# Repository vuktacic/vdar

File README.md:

# vdar

vdar is a low-cost 3D lidar scanner using the TF-Luna. It can generate point clouds of it's environment, which can be visualized with [vvis](./vvis). vdar is completely open source, and was designed for Hack Club's [Stasis program](https://stasis.hackclub.com). vdar was also exhibited at [Open Sauce 2026](https://www.opensauce.com/)

I created vdar because of a general interest in LiDAR. I've been playing with point clouds for a few years, and wanted to create a device that could generate my own clouds. I also wanted to learn how to create a mechanically more complex design, combined with designing and manufacturing an actual PCB.

[vdar Youtube Video](https://www.youtube.com/shorts/brxcMjVyBjw)

## Repo Structure

- [`./hardware`](./hardware) - Design files for vdar
  - [`./hardware/cad`](./hardware/cad) - Fusion 360 & Step design files for vdar
  - [`./hardware/pcb`](./hardware/pcb) - KiCad design files for vdar
    - [`./hardware/pcb/production`](./hardware/pcb/production) - PCB Production files (gerbers.zip)
- [`./JOURNAL.md`](./JOURNAL.md) - Development Journal for vdar
- [`./project`](./project) - Project management files for vdar
    - [`./project/assets`](./project/assets) - Media for project files
    - [`./project/docs`](./project/docs) - Assembly instructions for vdar
    - [`./project/finances`](./project/finances) - BOM & POs for vdar
- [`./vcore`](./vcore) - ESP32 firmware for vdar
- [`./vvis`](./vvis) - NodeJS visualizer for vdar

## Quick Start
Requirements:
 - PlatformIO Core
 - NodeJS
 - Python3

```bash
git clone https://github.com/vuktacic/vdar.git
cd vdar
just setup
mv ./vcore/include/secrets.h.example ./vcore/include/secrets.h
```
```bash
just build
just flash
just run
```

## Pictures
### Real life

### Scans

### 3D CAD

### PCB

### Offboard Wiring

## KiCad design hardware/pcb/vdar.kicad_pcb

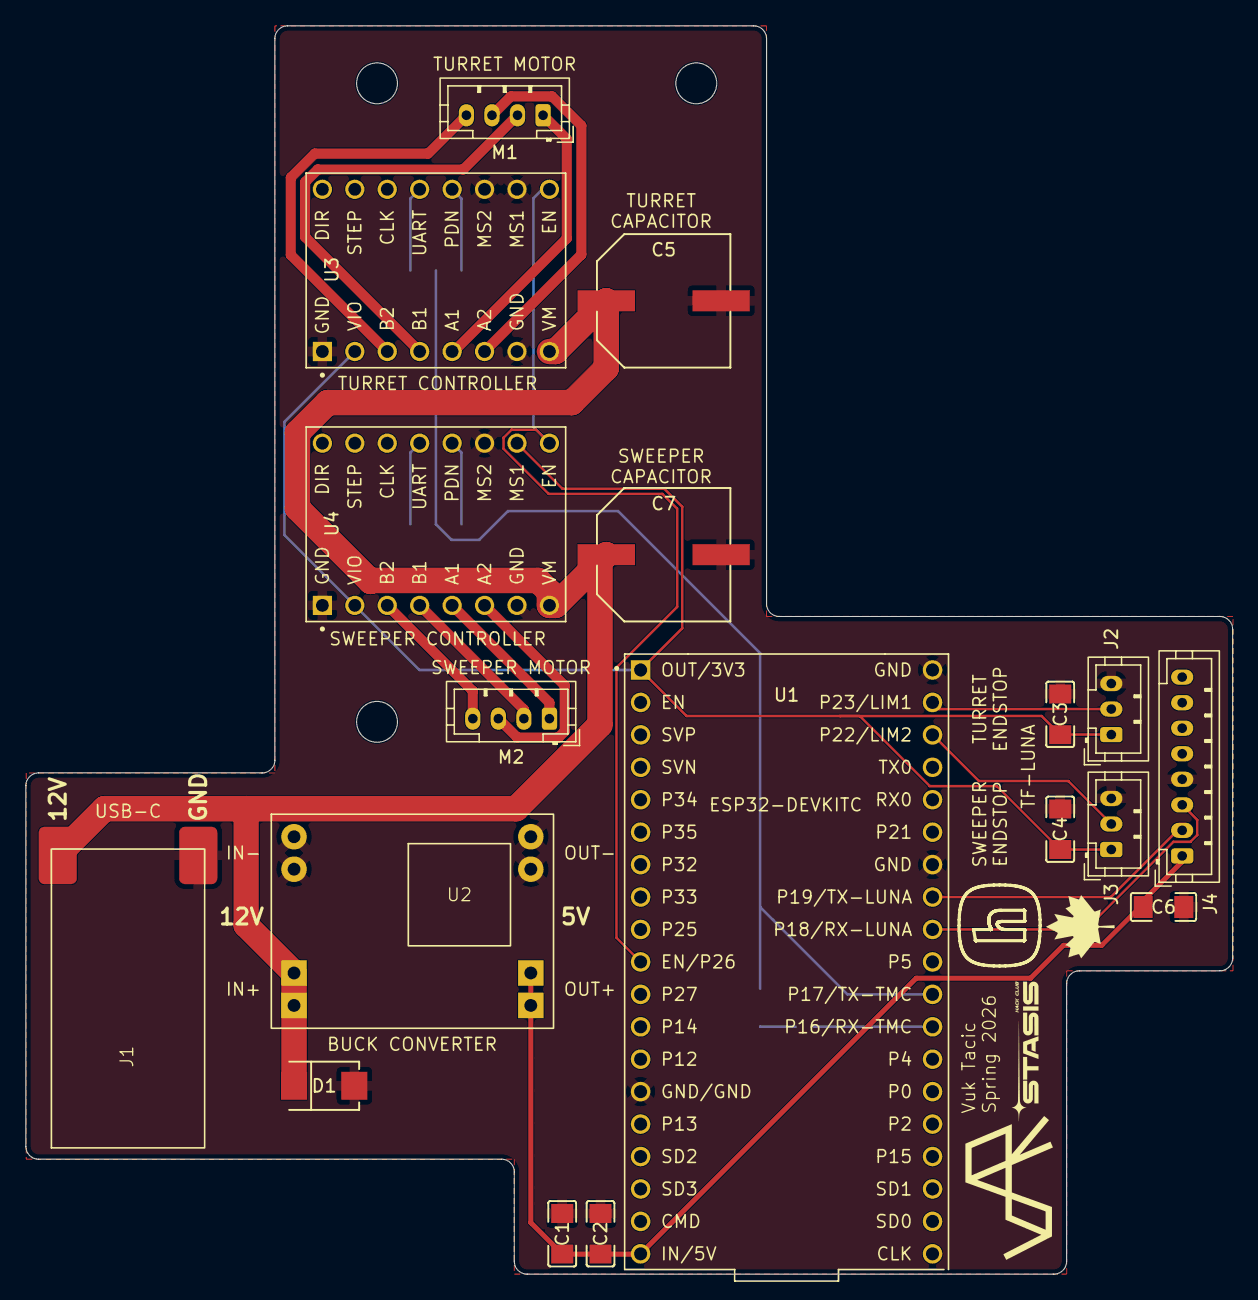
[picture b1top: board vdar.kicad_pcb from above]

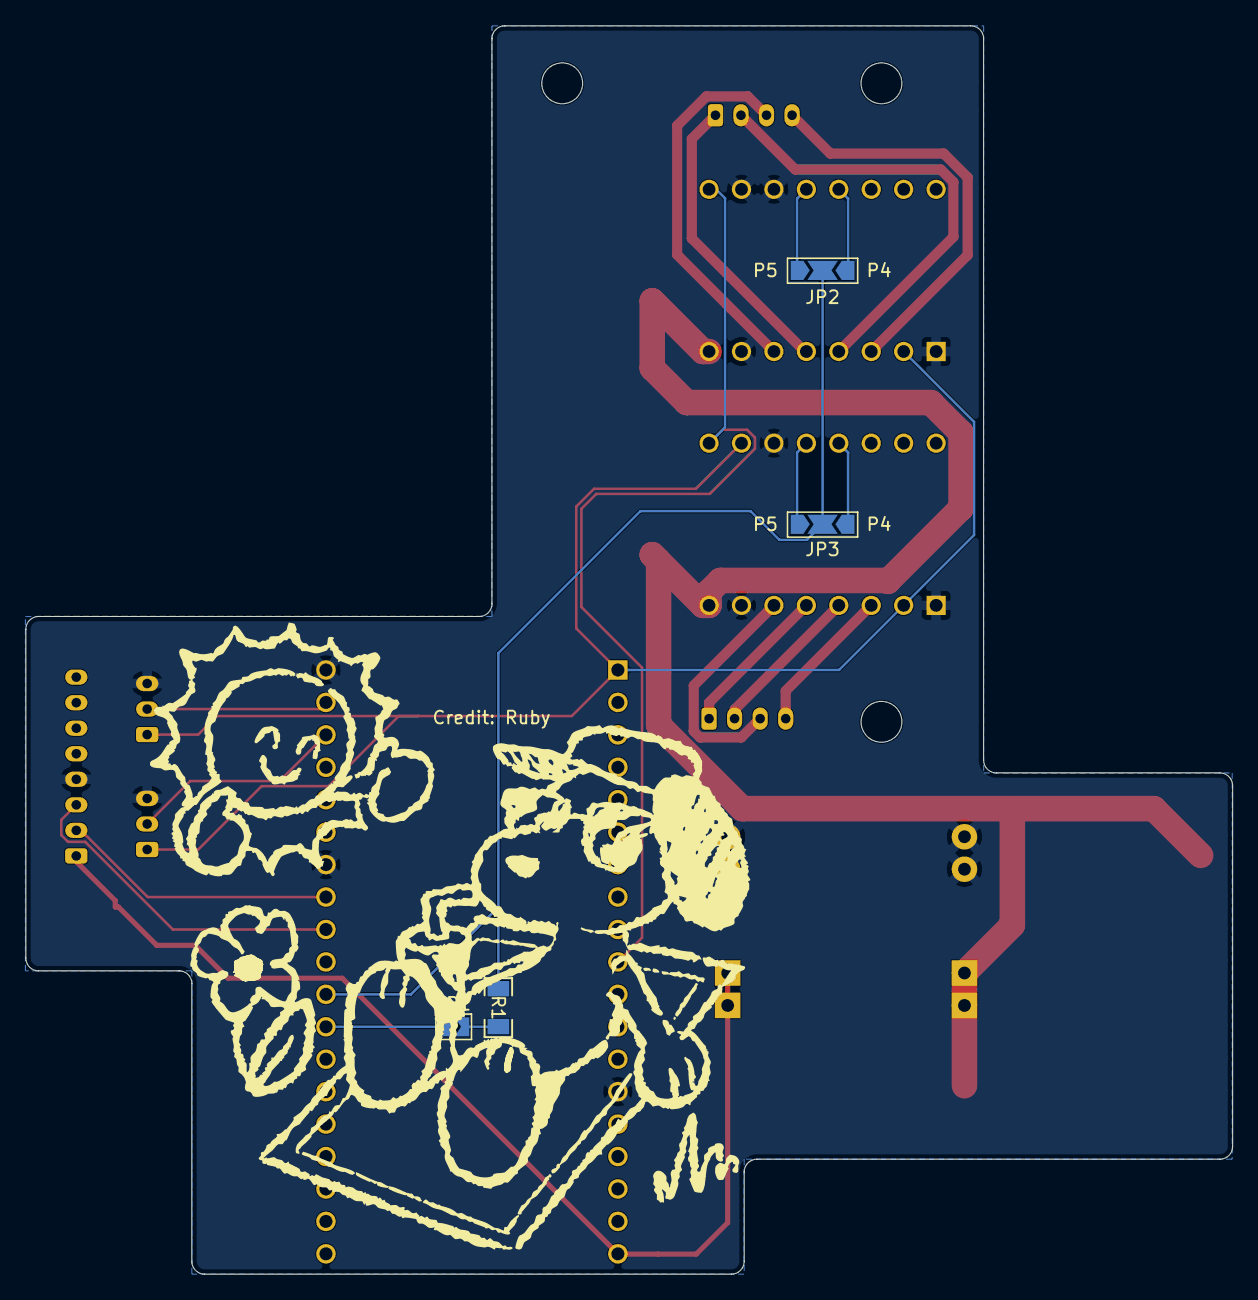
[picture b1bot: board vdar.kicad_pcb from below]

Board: 2 copper layers, 94.5 x 97.8 mm, 26 parts (4 on the bottom side), 24 nets.

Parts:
C1: 16V 10uF; C1206
C2, C3, C4, C6: 100V 100nF; C1206
C5, C7: 35V 470muF; CAP-SMD_BD10.0-L10.3-W10.3-LS11.0-FD
D1: 15Vrwm 16.7Vbr 24.4VC; SMB_L4.6-W3.6-LS5.3-RD
H1, H2, H3, H4: MountingHole; MountingHole_3.2mm_M3_Clearance
J1: USB C PD Board 12V 5A; USB_C_PD_BOARD
J2, J3: Optical Endstop; JST_PH_B3B-PH-K_1x03_P2.00mm_Vertical
J4: TF-LUNA; JST_PH_B8B-PH-K_1x08_P2.00mm_Vertical
JP1: SolderJumper_2_Open; SolderJumper-2_P1.3mm_Open_TrianglePad1.0x1.5mm
JP2, JP3: SolderJumper_3_Open; SolderJumper-3_P2.0mm_Open_TrianglePad1.0x1.5mm_NumberLabels
M1, M2: Nema 17; JST_PH_B4B-PH-K_1x04_P2.00mm_Vertical
R1: 1000Ω; R1206
U1: ESP32-DEVKITC; MODULE_ESP32-DEVKITC_VDAR
U2: MP1584EN Buck Converter; MP1584EN
U3, U4: TMC2209_SILENTSTEPSTICK; MODULE_TMC2209_SILENTSTEPSTICK_INTERNAL SILKSCREEN

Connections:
3.3V: C3.1, C4.1, J2.1, J3.1, U1.1 (3V3), U3.2 (VIO), U4.2 (VIO), U4.15 (MS1)
5V: C1.1, C2.1, C6.1, J4.1, U1.19 (EXT_5V), U2.1 (+VDC)
12V: C5.1, C7.1, D1.1, J1.A9 (VBUS), U2.5 (VIN+), U3.8 (VM), U4.8 (VM)
EN: U1.10 (IO26), U3.16 (~EN), U4.16 (~EN)
ESP-LUNA: J4.2, U1.31 (IO19)
ESP-TMC: JP2.2 (C), JP3.2 (C), R1.2, U1.28 (IO17)
GND: C1.2, C2.2, C3.2, C4.2, C5.2, C6.2, C7.2, D1.2, J1.A12 (GND), J2.3, J3.3, J4.4, U1.14 (GND1), U1.32 (GND2), U1.38 (GND3), U2.3 (-VDC), U2.7 (VIN-), U3.1 (GND), U3.7 (GND), U3.14 (MS2), U3.15 (MS1), U4.1 (GND), U4.7 (GND), U4.14 (MS2)
LIM1: J2.2, U1.37 (IO23)
LIM2: J3.2, U1.36 (IO22)
LUNA-ESP: J4.3, U1.30 (IO18)
M1A_1: M1.1 (-_1), U3.5 (M1A)
M1A_2: M2.1 (-_1), U4.5 (M1A)
M1B_1: M1.2, U3.4 (M1B)
M1B_2: M2.2, U4.4 (M1B)
M2A_1: M1.3, U3.6 (M2A)
M2A_2: M2.3, U4.6 (M2A)
M2B_1: M1.4, U3.3 (M2B)
M2B_2: M2.4, U4.3 (M2B)
unnamed: JP1.1 (A), U1.27 (IO16)
unnamed: JP1.2 (B), R1.1
unnamed: JP2.1 (A), U3.12 (UART)
unnamed: JP2.3 (B), U3.13 (PDN)
unnamed: JP3.1 (A), U4.12 (UART)
unnamed: JP3.3 (B), U4.13 (PDN)

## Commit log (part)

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2026-03-11 Add LICENSE
2026-03-11 Add folder structure
2026-03-11 Create PIO project
2026-03-11 Code workspace to fit PIO
2026-03-12 Rename Journal
2026-03-17 WIP BOM
2026-03-17 Nearly complete BOM
2026-03-20 Update BOM, Create TODO list, Start PCB
2026-03-24 Update Everything
2026-03-24 Add offboard wiring schematic
2026-03-24 Complete Bill of Materials
2026-03-24 Swap bolt vendors
2026-03-24 Change CSV Separator
2026-03-24 Fix formatting in purchase_order.csv
2026-03-24 Update BOM & Fastenal PO
2026-03-25 Minor BoM vendor update (ali -> lee's)
2026-03-25 Optimize timing belt
2026-03-25 Major firmware changes
2026-03-26 Firmware done
2026-03-26 Rename firmware, software --> vcore, vvis
2026-03-26 Update BoM/PO
2026-03-26 Visualizer
2026-03-26 Update Sweep & status sending
2026-03-26 Finish vvis
2026-03-26 Add gerbers & update readmes
2026-03-26 Add vdar_pcb.zip
2026-03-26 Fix README.md image
2026-03-29 Add silkscreen to PCB
2026-04-03 Fix formatting
2026-04-03 Add Justfile
2026-04-03 Move finances & Add assembly
2026-04-03 Add instructions to readme
2026-04-07 Update on-hand materials
2026-04-09 Add WIRENETS.md
2026-04-30 Working motors, endstops, & lidar readings
2026-05-13 Spinning!
2026-05-13 vcore working
2026-05-13 Readd vvis
2026-05-15 Finished!
2026-06-08 Add images
